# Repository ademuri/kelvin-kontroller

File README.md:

# Kelvin Kontroller

DIY coffee roaster. Custom PCB which controls and monitors the roaster. Has a WiFi dashboard.

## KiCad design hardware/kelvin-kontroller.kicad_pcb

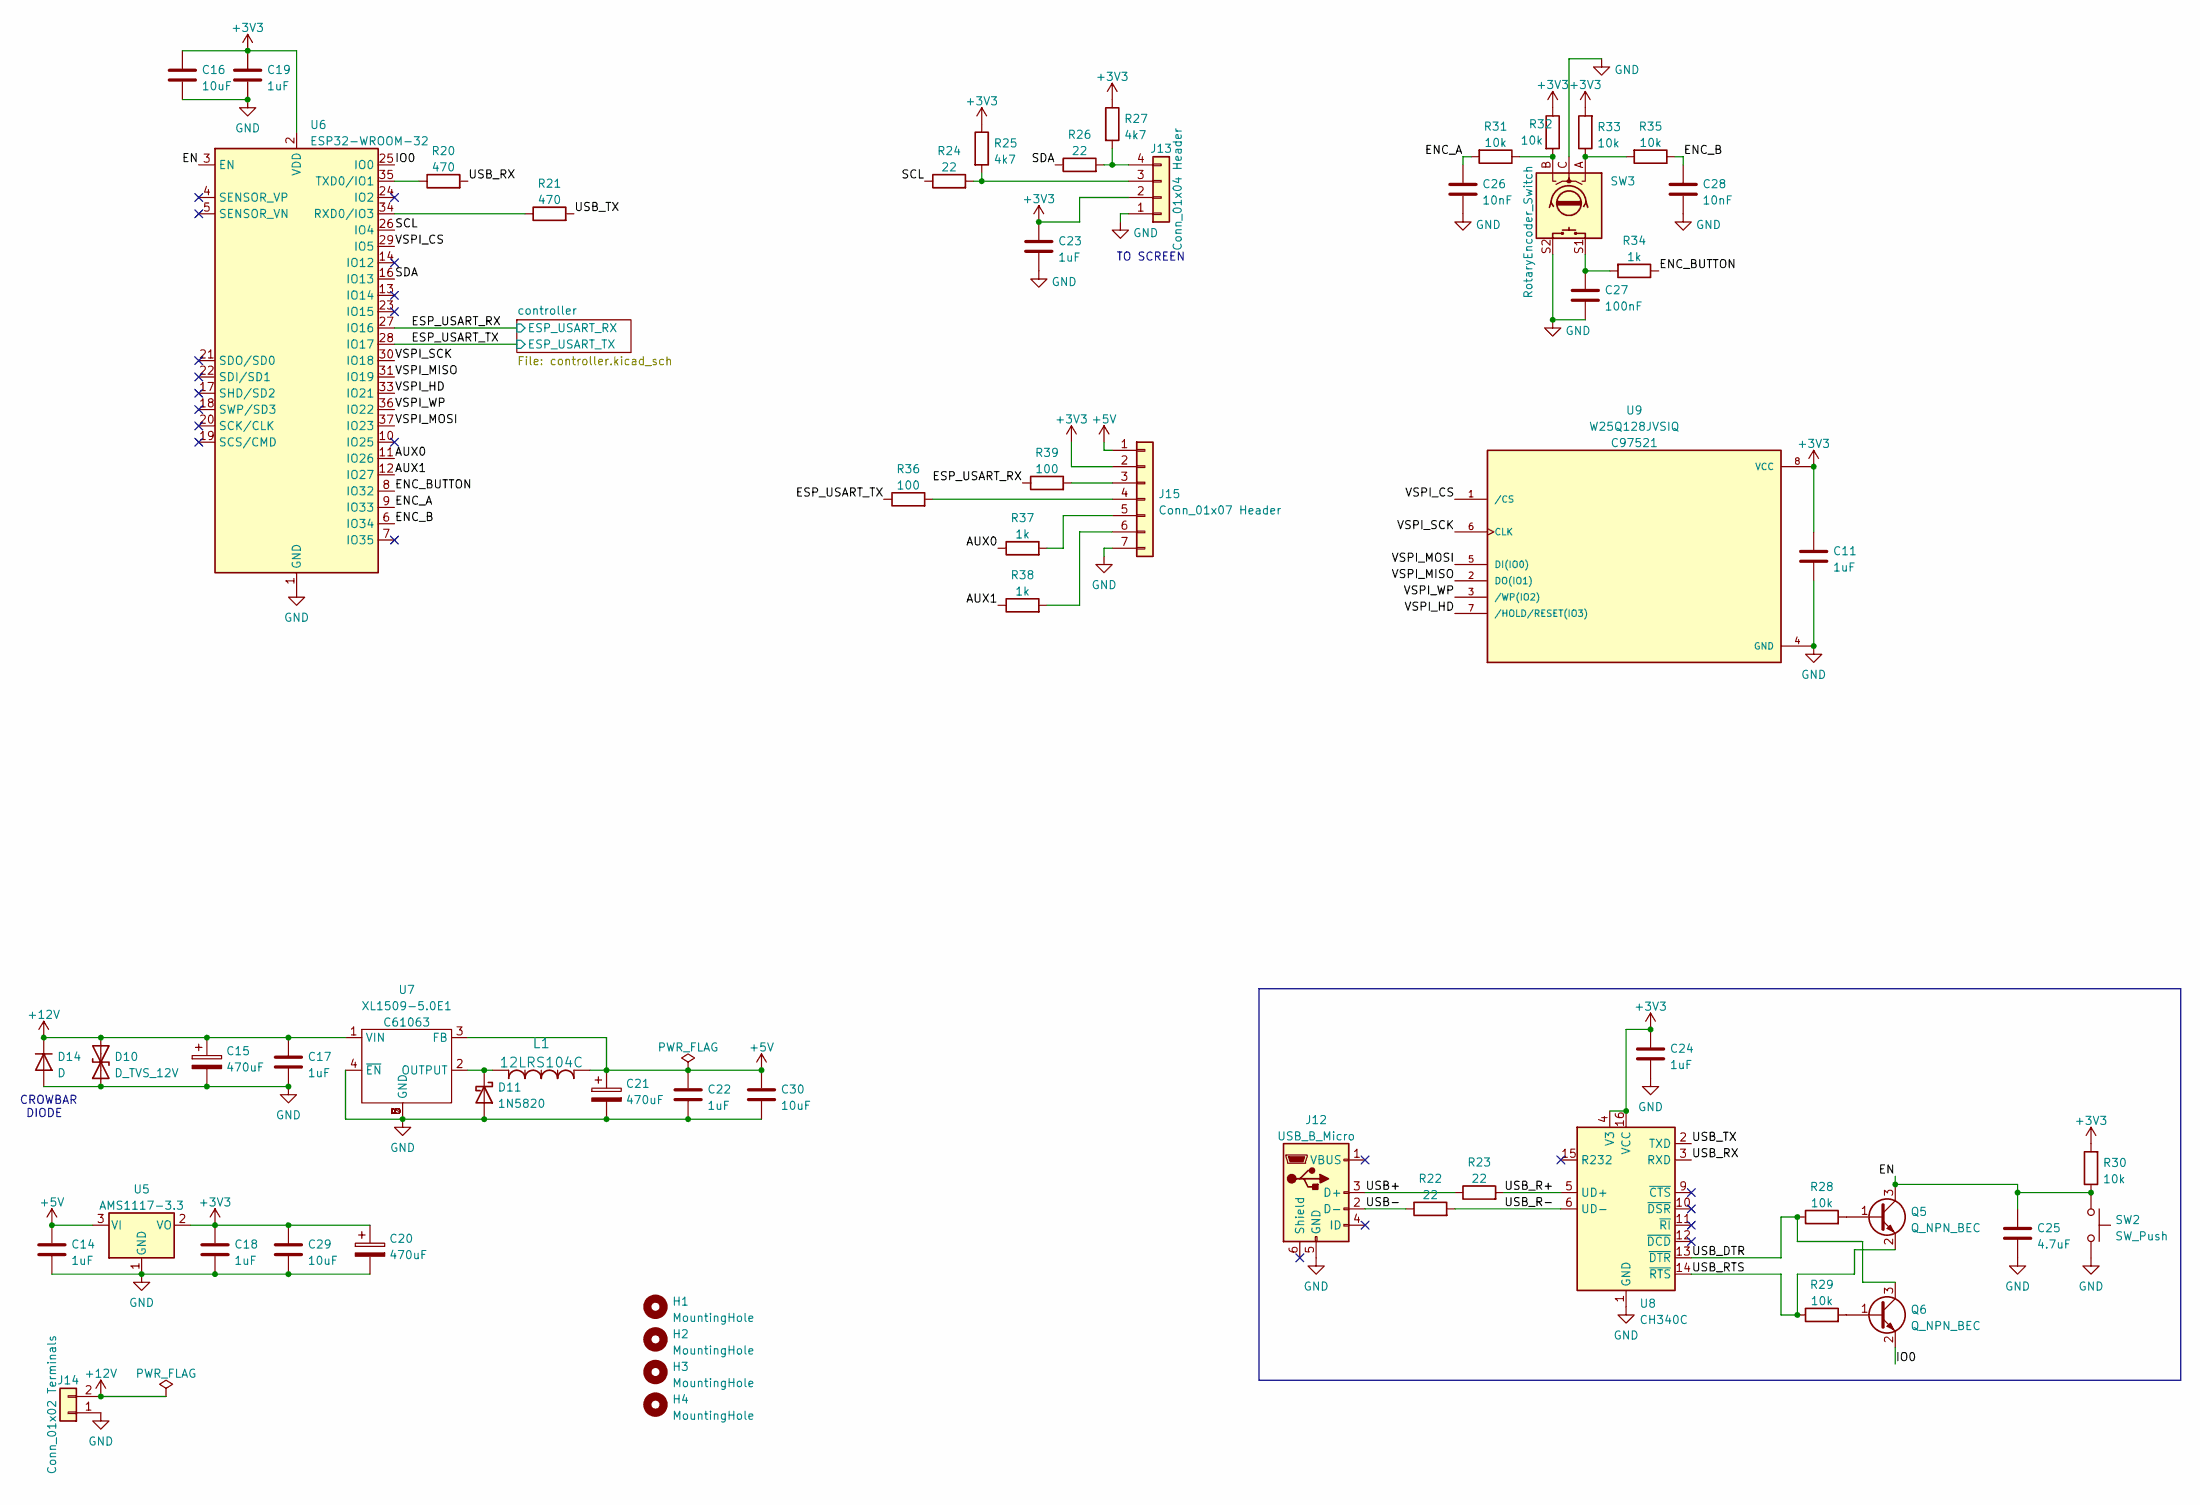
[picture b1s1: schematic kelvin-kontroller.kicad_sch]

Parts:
C11, C14, C17, C18, C19, C22, C23, C24: 1uF; C_0402_1005Metric; LCSC C52923
C15, C20, C21: 470uF; CP_Radial_D10.0mm_P5.00mm; MPN 25PK1000MEFC10X16
C16, C29, C30: 10uF; C_0603_1608Metric; LCSC C96446
C25: 4.7uF; C_0402_1005Metric; LCSC C23733
C26, C28: 10nF; C_0402_1005Metric; LCSC C15195
C27: 100nF; C_0402_1005Metric; LCSC C307331
D10: D_TVS_12V; D_SMA_Handsoldering; MPN 824501131
D11: 1N5820; D_SMA; LCSC C8678
D14: D; D_SMA; LCSC C8678
H1, H2, H3, H4: MountingHole; MountingHole_3.2mm_M3
J12: USB_B_Micro; FRAMATOME_10118194-0001LF_fixed_bridges; LCSC C132563
J13: Conn_01x04 Header; PinHeader_1x04_P2.54mm_Vertical
J14: Conn_01x02 Terminals; Amphenol_BarrierStrip_YK321020XX00G_1x02_P7.62; MPN YK3210203000G
J15: Conn_01x07 Header; PinHeader_1x07_P2.54mm_Vertical
L1: 12LRS104C; MPN 12LRS104C
Q5, Q6: Q_NPN_BEC; SOT-23; LCSC C2150
R20, R21: 470; R_0402_1005Metric; LCSC C25117
R22, R23, R24, R26: 22; R_0402_1005Metric; LCSC C25092
R25, R27: 4k7; R_0402_1005Metric; LCSC C25900
R28, R29, R30, R31, R32, R33, R35: 10k; R_0402_1005Metric; LCSC C25744
R34, R37, R38: 1k; R_0402_1005Metric; LCSC C11702
R36, R39: 100; R_0402_1005Metric; LCSC C25076
SW2: SW_Push; SW_TACTILE_5.1MM_TS-1187A-C-D-B; LCSC C318884
SW3: RotaryEncoder_Switch; BOURNS_PEC12R-4xxxF-Sxxxx; MPN PEC12R-4230F-S0024
U5: AMS1117-3.3; SOT-223-3_TabPin2; LCSC C6186
U6: ESP32-WROOM-32
U7: XL1509-5.0E1; SOIC-8_5.23x5.23mm_P1.27mm; LCSC C61063
U8: CH340C; SOIC-16_3.9x9.9mm_P1.27mm; LCSC C84681
U9: W25Q128JVSIQ; SOIC-8_5.275x5.275mm_P1.27mm; PARTREV I; LCSC C97521

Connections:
+3V3: C11.1, C16.1, C18.1, C19.1, C20.1, C23.1, C24.1, C29.1, J13.2, J15.2, R25.1, R27.1, R30.2, R32.1, R33.2, U5.2 (VO), U6.2 (VDD), U8.4 (V3), U8.16 (VCC), U9.8 (VCC); also elsewhere on the board
+5V: C14.1, C21.1, C22.1, C30.1, J15.1, L1.3, U5.3 (VI), U7.3 (FB); also elsewhere on the board
+12V: C15.1, C17.1, D10.2 (A2), D14.1 (K), J14.2, U7.1 (VIN); also elsewhere on the board
/AUX0: R37.1, U6.11 (IO26)
/AUX1: R38.1, U6.12 (IO27)
/EN: C25.1, Q5.3 (C), R30.1, SW2.1, U6.3 (EN)
/ENC_A: C26.1, R31.2, U6.9 (IO33)
/ENC_B: C28.1, R35.1, U6.6 (IO34)
/ENC_BUTTON: R34.1, U6.8 (IO32)
/ESP_USART_RX: R39.1, U6.27 (IO16); also elsewhere on the board
/ESP_USART_TX: R36.1, U6.28 (IO17); also elsewhere on the board
/IO0: Q6.2 (E), U6.25 (IO0)
/SCL: R24.1, U6.26 (IO4)
/SDA: R26.1, U6.16 (IO13)
/USB+: J12.3 (D+), R23.1
/USB-: J12.2 (D-), R22.1
/USB_DTR: Q6.3 (C), R28.1, U8.13 (~DTR)
/USB_R+: R23.2, U8.5 (UD+)
/USB_R-: R22.2, U8.6 (UD-)
/USB_RTS: Q5.2 (E), R29.1, U8.14 (~RTS)
/USB_RX: R20.2, U8.3 (RXD)
/USB_TX: R21.2, U8.2 (TXD)
/VSPI_CS: U6.29 (IO5), U9.1 (/CS)
/VSPI_HD: U6.33 (IO21), U9.7 (/HOLD/RESET(IO3))
/VSPI_MISO: U6.31 (IO19), U9.2 (DO(IO1))
/VSPI_MOSI: U6.37 (IO23), U9.5 (DI(IO0))
/VSPI_SCK: U6.30 (IO18), U9.6 (CLK)
/VSPI_WP: U6.36 (IO22), U9.3 (/WP(IO2))
GND: C11.2, C14.2, C15.2, C16.2, C17.2, C18.2, C19.2, C20.2, C21.2, C22.2, C23.2, C24.2, C25.2, C26.2, C27.2, C28.2, C29.2, C30.2, D10.1 (A1), D11.2 (A), D14.2 (A), J12.5 (GND), J13.1, J14.1, J15.7, SW2.2, SW3.C, SW3.S2, U5.1 (GND), U6.1 (GND), U6.15 (GND), U6.38 (GND), U6.39 (GND), U7.4 (~EN), U7.5 (GND), U7.6 (GND), U7.7 (GND), U7.8 (GND), U8.1 (GND), U9.4 (GND); also elsewhere on the board
unnamed: C27.1, R34.2, SW3.S1
unnamed: D11.1 (K), L1.1, U7.2 (OUTPUT)
unnamed: J13.3, R24.2, R25.2
unnamed: J13.4, R26.2, R27.2
unnamed: J15.3, R39.2
unnamed: J15.4, R36.2
unnamed: J15.5, R37.2
unnamed: J15.6, R38.2
unnamed: Q5.1 (B), R28.2
unnamed: Q6.1 (B), R29.2
unnamed: R20.1, U6.35 (TXD0/IO1)
unnamed: R21.1, U6.34 (RXD0/IO3)
unnamed: R31.1, R32.2, SW3.B
unnamed: R33.1, R35.2, SW3.A

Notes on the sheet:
CROWBAR DIODE
TO SCREEN

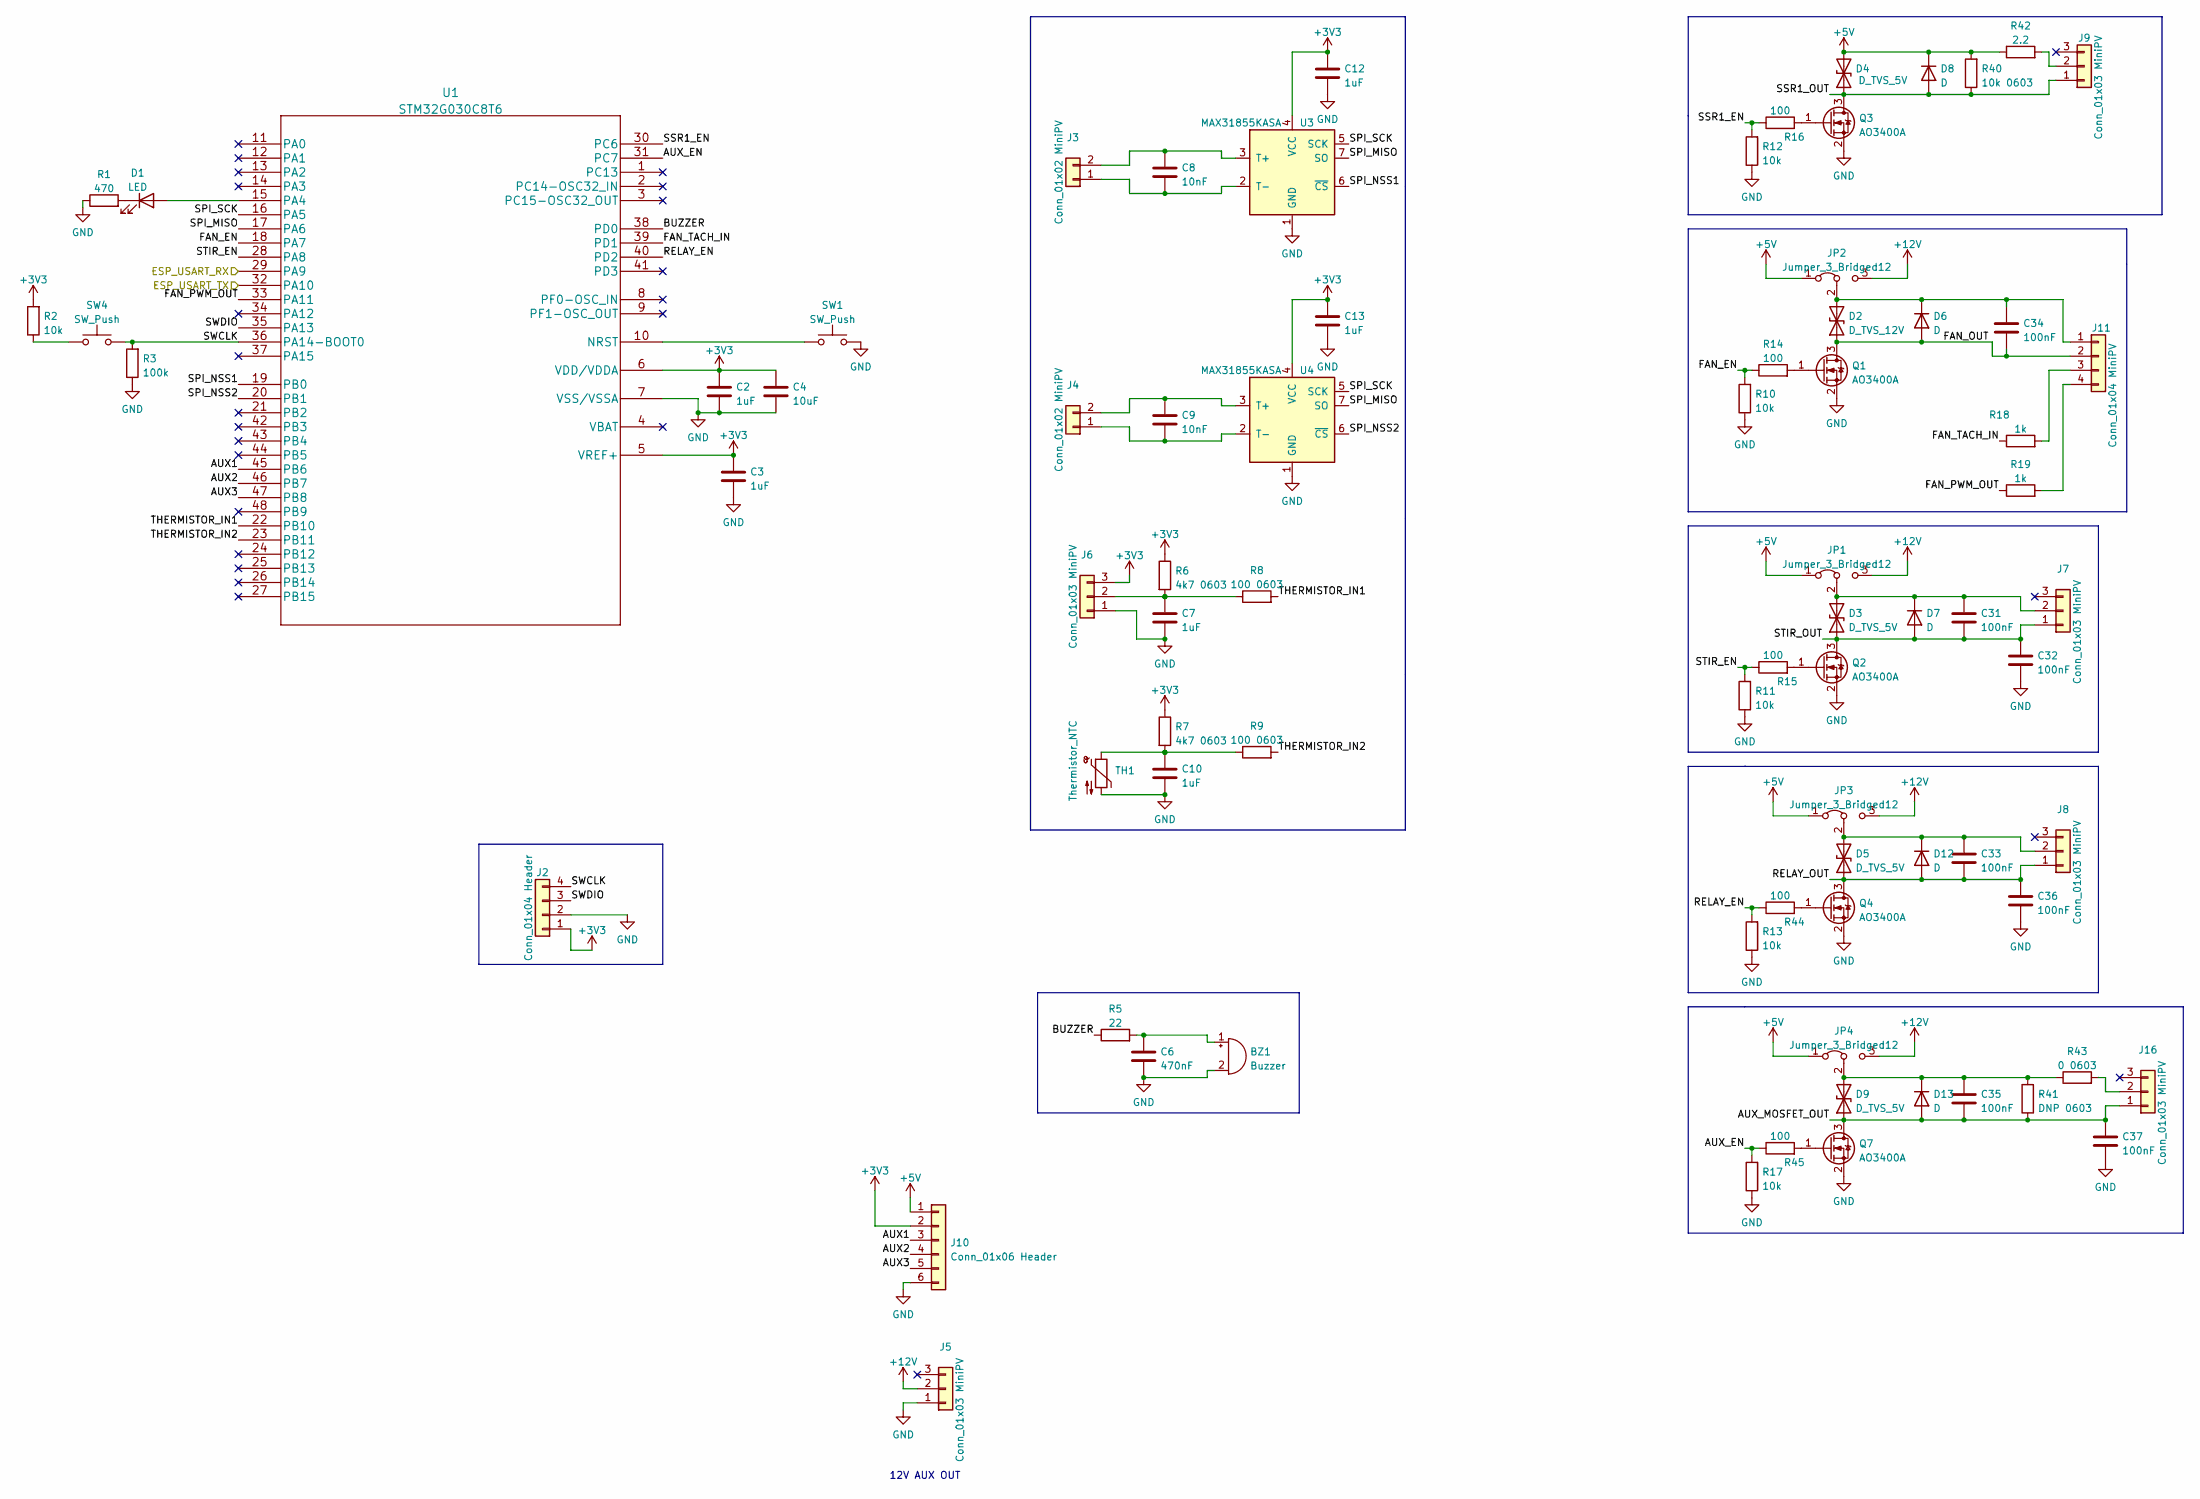
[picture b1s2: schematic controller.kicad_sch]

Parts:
BZ1: Buzzer; MURATA_PKM13EPYH4000-A0; MPN PKM13EPYH4000-A0
C2, C3, C7, C10, C12, C13: 1uF; C_0402_1005Metric; LCSC C52923
C4: 10uF; C_0603_1608Metric; LCSC C96446
C6: 470nF; C_0402_1005Metric; LCSC C47339
C8, C9: 10nF; C_0402_1005Metric; LCSC C15195
C31, C32, C33, C34, C35, C36, C37: 100nF; C_0402_1005Metric; LCSC C307331
D1: LED; LED_0805_2012Metric; LCSC C84256
D2: D_TVS_12V; D_SMA_Handsoldering; MPN 824501131
D3, D4, D5, D9: D_TVS_5V; D_SMA_Handsoldering; MPN 824501600
D6, D7, D8, D12, D13: D; D_SMA; LCSC C8678
J2: Conn_01x04 Header; PinHeader_1x04_P2.54mm_Vertical
J3, J4: Conn_01x02 MiniPV; MiniPV_76384-X02XX_1x02_P2.54mm_Vertical
J5, J6, J7, J8, J9, J16: Conn_01x03 MiniPV; MiniPV_69167-X03XXX_1x03_P2.54mm_Polarized_Vertical
J10: Conn_01x06 Header; PinHeader_1x06_P2.54mm_Vertical
J11: Conn_01x04 MiniPV; MiniPV_69167-X04XXX_1x04_P2.54mm_Polarized_Vertical
JP1, JP2, JP3, JP4: Jumper_3_Bridged12; PinHeader_1x03_P2.54mm_Vertical
Q1, Q2, Q3, Q4, Q7: AO3400A; SOT-23; LCSC C20917
R1: 470; R_0402_1005Metric; LCSC C25117
R2, R10, R11, R12, R13, R17: 10k; R_0402_1005Metric; LCSC C25744
R3: 100k; R_0402_1005Metric; LCSC C25741
R5: 22; R_0402_1005Metric; LCSC C25092
R6, R7: 4k7 0603; R_0603_1608Metric_Pad0.98x0.95mm_HandSolder; LCSC C23162
R8, R9: 100 0603; R_0603_1608Metric_Pad0.98x0.95mm_HandSolder; LCSC C22775
R14, R15, R16, R44, R45: 100; R_0402_1005Metric; LCSC C25076
R18, R19: 1k; R_0402_1005Metric; LCSC C11702
R40: 10k 0603; R_0603_1608Metric_Pad0.98x0.95mm_HandSolder; LCSC C25804
R41: DNP 0603; R_0603_1608Metric_Pad0.98x0.95mm_HandSolder; LCSC C25804
R42: 2.2; R_0603_1608Metric_Pad0.98x0.95mm_HandSolder; LCSC C22939
R43: 0 0603; R_0603_1608Metric_Pad0.98x0.95mm_HandSolder; LCSC C22939
SW1, SW4: SW_Push; SW_TACTILE_5.1MM_TS-1187A-C-D-B; LCSC C318884
TH1: Thermistor_NTC; C_Disc_D3.0mm_W2.0mm_P2.50mm; MPN NXRT15XH103FA1B030
U1: STM32G030C8T6; LQFP-48_7x7mm_P0.5mm; LCSC C529329
U3, U4: MAX31855KASA; SOIC-8_3.9x4.9mm_P1.27mm; LCSC C52028

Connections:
+3V3: C2.1, C3.1, C4.1, C12.1, C13.1, J2.1, J6.3, J10.2, R2.2, R6.1, R7.1, U1.5 (VREF+), U1.6 (VDD/VDDA), U3.4 (VCC), U4.4 (VCC); also elsewhere on the board
+5V: D4.2 (A2), D8.1 (K), J10.1, JP1.1 (A), JP2.1 (A), JP3.1 (A), JP4.1 (A), R40.2, R42.1; also elsewhere on the board
+12V: J5.2, JP1.3 (B), JP2.3 (B), JP3.3 (B), JP4.3 (B); also elsewhere on the board
/ESP_USART_RX: U1.29 (PA9); also elsewhere on the board
/ESP_USART_TX: U1.32 (PA10); also elsewhere on the board
/controller/AUX1: J10.3, U1.45 (PB6)
/controller/AUX2: J10.4, U1.46 (PB7)
/controller/AUX3: J10.5, U1.47 (PB8)
/controller/AUX_EN: R17.2, R45.1, U1.31 (PC7)
/controller/AUX_MOSFET_OUT: C35.2, C37.1, D9.1 (A1), D13.2 (A), J16.1, Q7.3 (D), R41.1
/controller/BUZZER: R5.1, U1.38 (PD0)
/controller/FAN_EN: R10.2, R14.1, U1.18 (PA7)
/controller/FAN_OUT: C34.2, D2.1 (A1), D6.2 (A), J11.2, Q1.3 (D)
/controller/FAN_PWM_OUT: R19.1, U1.33 (PA11)
/controller/FAN_TACH_IN: R18.1, U1.39 (PD1)
/controller/RELAY_EN: R13.2, R44.1, U1.40 (PD2)
/controller/RELAY_OUT: C33.2, C36.1, D5.1 (A1), D12.2 (A), J8.1, Q4.3 (D)
/controller/SPI_MISO: U1.17 (PA6), U3.7 (SO), U4.7 (SO)
/controller/SPI_NSS1: U1.19 (PB0), U3.6 (~CS)
/controller/SPI_NSS2: U1.20 (PB1), U4.6 (~CS)
/controller/SPI_SCK: U1.16 (PA5), U3.5 (SCK), U4.5 (SCK)
/controller/SSR1_EN: R12.2, R16.1, U1.30 (PC6)
/controller/SSR1_OUT: D4.1 (A1), D8.2 (A), J9.1, Q3.3 (D), R40.1
/controller/STIR_EN: R11.2, R15.1, U1.28 (PA8)
/controller/STIR_OUT: C31.2, C32.1, D3.1 (A1), D7.2 (A), J7.1, Q2.3 (D)
/controller/SWCLK: J2.4, R3.2, SW4.2, U1.36 (PA14-BOOT0)
/controller/SWDIO: J2.3, U1.35 (PA13)
/controller/THERMISTOR_IN1: R8.2, U1.22 (PB10)
/controller/THERMISTOR_IN2: R9.2, U1.23 (PB11)
GND: BZ1.2 (+), C2.2, C3.2, C4.2, C6.2, C7.2, C10.2, C12.2, C13.2, C32.2, C36.2, C37.2, J2.2, J5.1, J6.1, J10.6, Q1.2 (S), Q2.2 (S), Q3.2 (S), Q4.2 (S), Q7.2 (S), R1.1, R3.1, R10.1, R11.1, R12.1, R13.1, R17.1, SW1.2, TH1.2, U1.7 (VSS/VSSA), U3.1 (GND), U4.1 (GND); also elsewhere on the board
unnamed: BZ1.1 (-), C6.1, R5.2
unnamed: C7.1, J6.2, R6.2, R8.1
unnamed: C8.1, J3.2, U3.3 (T+)
unnamed: C8.2, J3.1, U3.2 (T-)
unnamed: C9.1, J4.2, U4.3 (T+)
unnamed: C9.2, J4.1, U4.2 (T-)
unnamed: C10.1, R7.2, R9.1, TH1.1
unnamed: C31.1, D3.2 (A2), D7.1 (K), J7.2, JP1.2 (C)
unnamed: C33.1, D5.2 (A2), D12.1 (K), J8.2, JP3.2 (C)
unnamed: C34.1, D2.2 (A2), D6.1 (K), J11.1, JP2.2 (C)
unnamed: C35.1, D9.2 (A2), D13.1 (K), JP4.2 (C), R41.2, R43.1
unnamed: D1.1 (K), R1.2
unnamed: D1.2 (A), U1.15 (PA4)
unnamed: J9.2, R42.2
unnamed: J11.3, R18.2
unnamed: J11.4, R19.2
unnamed: J16.2, R43.2
unnamed: Q1.1 (G), R14.2
unnamed: Q2.1 (G), R15.2
unnamed: Q3.1 (G), R16.2
unnamed: Q4.1 (G), R44.2
unnamed: Q7.1 (G), R45.2
unnamed: R2.1, SW4.1
unnamed: SW1.1, U1.10 (NRST)

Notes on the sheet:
12V AUX OUT

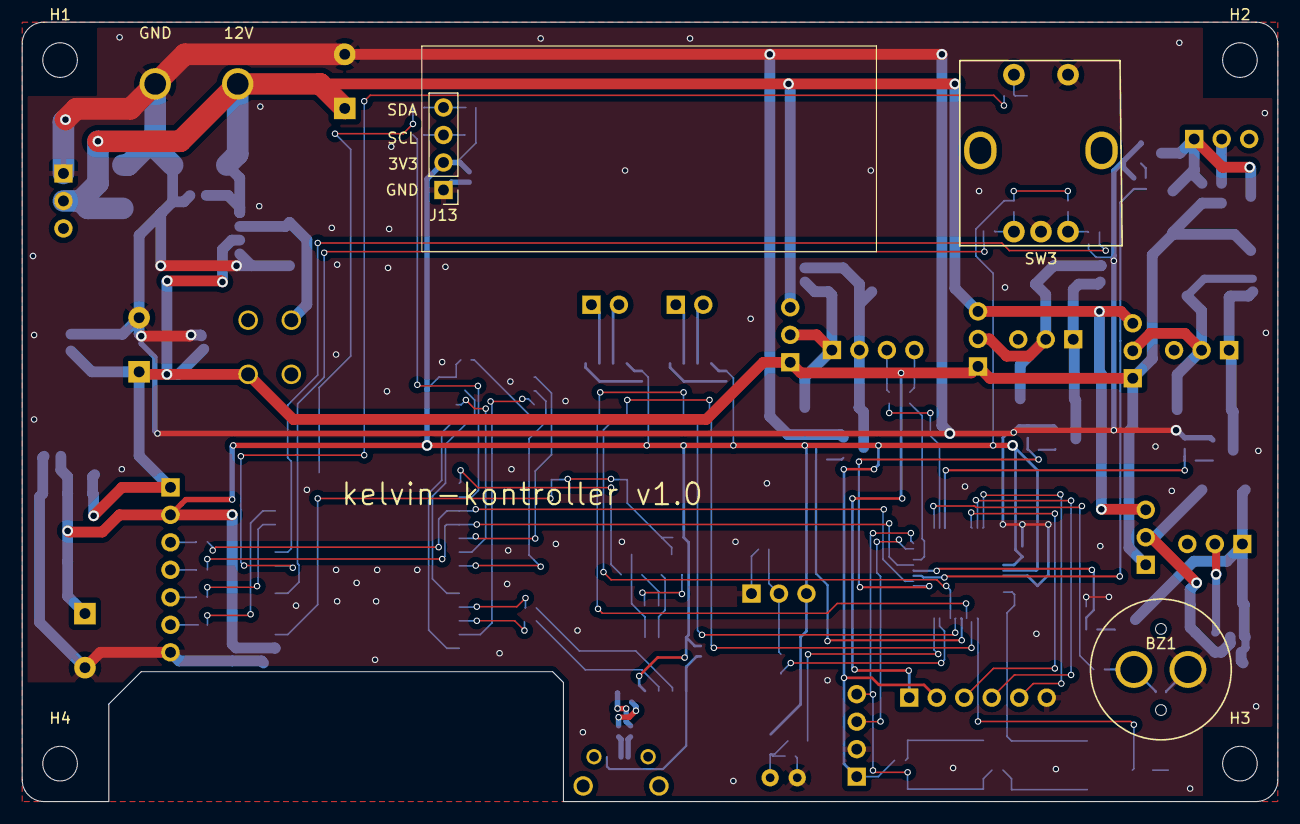
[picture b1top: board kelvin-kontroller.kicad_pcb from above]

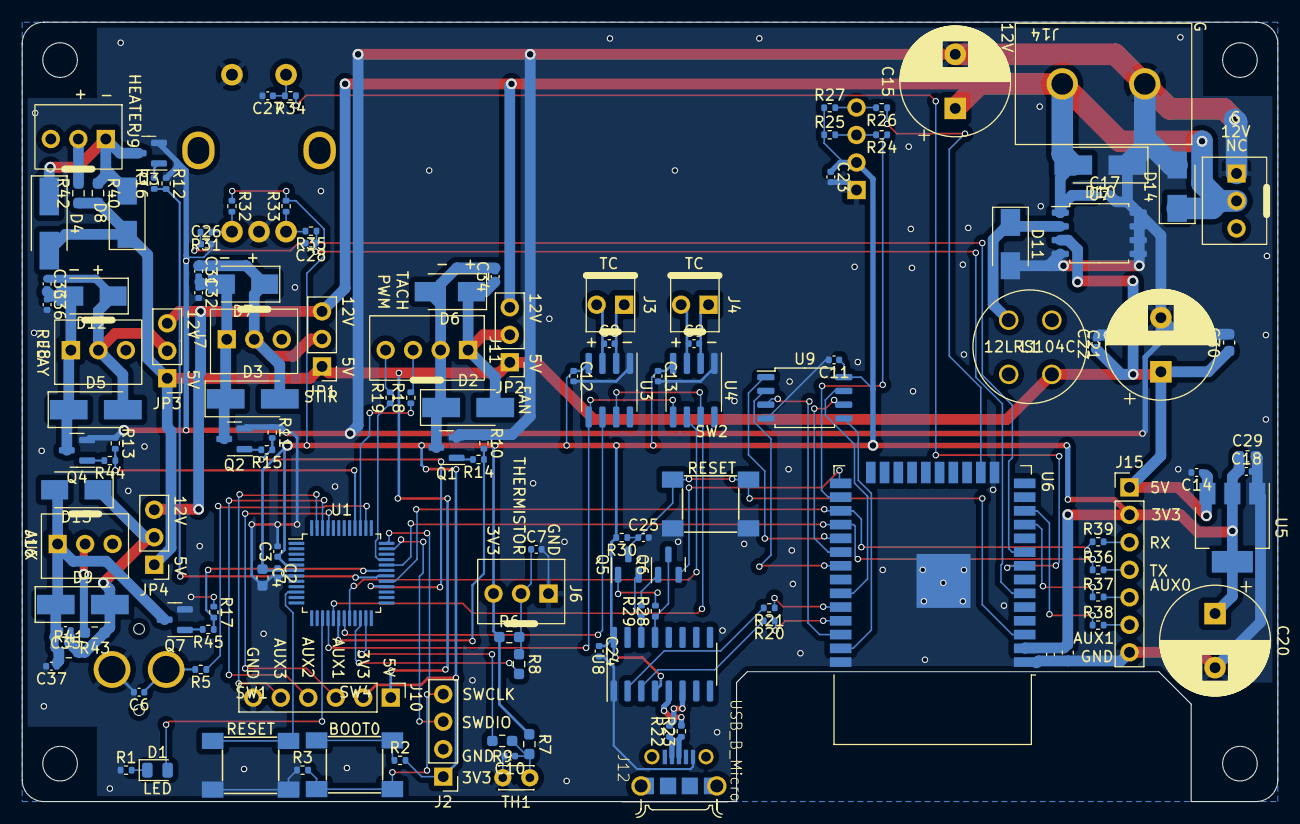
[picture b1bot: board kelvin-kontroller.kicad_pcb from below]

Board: 2 copper layers, 116.0 x 72.0 mm, 138 parts (131 on the bottom side), 91 nets.

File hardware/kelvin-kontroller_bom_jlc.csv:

"Comment","Designator","Footprint","LCSC Part #"
"470nF","C6","C_0402_1005Metric","C47339"
"1uF","C11,C14,C17,C18,C19,C22,C23,C24,C2,C3,C7,C10,C12,C13","C_0402_1005Metric","C52923"
"10uF","C16,C29,C30,C4","C_0603_1608Metric","C96446"
"4.7uF","C25","C_0402_1005Metric","C23733"
"10nF","C26,C28,C8,C9","C_0402_1005Metric","C15195"
"100nF","C27,C31,C32,C33,C34,C35,C36,C37","C_0402_1005Metric","C307331"
"LED","D1","LED_0805_2012Metric","C84256"
"1N5820","D11","D_SMA","C8678"
"D","D14,D6,D7,D8,D12,D13","D_SMA","C8678"
"USB_B_Micro","J12","FRAMATOME_10118194-0001LF_fixed_bridges","C132563"
"AO3400A","Q1,Q2,Q3,Q4,Q7","SOT-23","C20917"
"Q_NPN_BEC","Q5,Q6","SOT-23","C2150"
"100k","R3","R_0402_1005Metric","C25741"
"4k7 0603","R6,R7","R_0603_1608Metric_Pad0.98x0.95mm_HandSolder","C23162"
"100 0603","R8,R9","R_0603_1608Metric_Pad0.98x0.95mm_HandSolder","C22775"
"470","R20,R21,R1","R_0402_1005Metric","C25117"
"22","R22,R23,R24,R26,R5","R_0402_1005Metric","C25091"
"4k7","R25,R27","R_0402_1005Metric","C25900"
"10k","R28,R29,R30,R31,R32,R33,R35,R2,R10,R11,R12,R13,R17","R_0402_1005Metric","C25744"
"1k","R34,R37,R38,R18,R19","R_0402_1005Metric","C11702"
"100","R36,R39,R14,R15,R16,R44,R45","R_0402_1005Metric","C25076"
"10k 0603","R40","R_0603_1608Metric_Pad0.98x0.95mm_HandSolder","C25804"
"DNP 0603","R41","R_0603_1608Metric_Pad0.98x0.95mm_HandSolder","C25804"
"2.2","R42","R_0603_1608Metric_Pad0.98x0.95mm_HandSolder","C22939"
"0 0603","R43","R_0603_1608Metric_Pad0.98x0.95mm_HandSolder","C22939"
"SW_Push","SW2,SW1,SW4","SW_TACTILE_5.1MM_TS-1187A-C-D-B","C318884"
"STM32G030C8T6","U1","LQFP-48_7x7mm_P0.5mm","C529329"
"MAX31855KASA","U3,U4","SOIC-8_3.9x4.9mm_P1.27mm","C52028"
"AMS1117-3.3","U5","SOT-223-3_TabPin2","C6186"
"XL1509-5.0E1","U7","SOIC-8_5.23x5.23mm_P1.27mm","C61063"
"CH340C","U8","SOIC-16_3.9x9.9mm_P1.27mm","C84681"
"W25Q128JVSIQ","U9","SOIC-8_5.275x5.275mm_P1.27mm","C97521"

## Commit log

2022-10-03 Start adding schematic
2022-10-04 Add KiCAD gitignore
2022-10-04 Continue schematic - finish controller and add LCD
2022-10-05 Schematic nearly finished
2022-10-06 Update schematic and part assignment
2022-10-06 Add readme and license
2022-10-07 Finish assigning footprints
2022-10-10 Start layout
2022-10-11 Add internal thermistor and change SSR2 -> mosfet
2022-10-11 Continue layout, add SPI flash
2022-10-12 Continue layout
2022-10-13 First pass at layout
2022-10-13 Start routing
2022-10-14 Hardware revision v1.0
2022-10-16 Init platformio for both mcus
2022-10-16 Add pin definitions for stm32
2022-10-18 Add controls for heater, and min/max settings
2022-10-18 Add github actions config
2022-10-18 Add getters and stir control to controller
2022-10-18 Add Init and Step to controller
2022-10-18 Start adding thermistor class (not working yet)
2022-10-19 Fix thermistor and add Celsius/Fahrenheit methods
2022-10-19 Enable ASAN and UBSAN for tests
2022-10-19 Configure CI to run tests
2022-10-19 Format thermistor files
2022-10-20 Add function to read resistance to thermistor
2022-10-20 Add ReadFahrenheit convenience method
2022-10-20 Add thermocouple classes
2022-10-21 Initialize SPI
2022-10-21 Add filtering for temps
2022-10-22 Add basic error handling to runner
2022-10-22 Start adding test coverage for controller
2022-10-22 Complete test coverage for controller min/max temps
2022-10-22 Check that the controller turns on the relay at init
2022-10-22 Check for thermocouple read errors in controller
2022-10-22 Set temps in RunnerStatus
2022-10-22 Change heater to be on/off in the controller
2022-10-22 Add a command struct
2022-10-22 Add lint script and format files
2022-10-25 Add serial comms to runner
2022-10-25 Start adding websockets support
    Currently untested.
2022-10-26 Use easy transfer between esp32 and stm32
2022-10-26 Add a comms timeout to controller
2022-10-27 Fault on no comms
2022-10-27 Switch from websockets to modbus and implement read
2022-10-28 Mostly add modbus write
2022-10-28 Revert "Mostly add modbus write"
    This reverts commit 60ff8b54a95f325f4c3ebfb928f32a231f997c20.
2022-10-28 Revert "Switch from websockets to modbus and implement read"
    This reverts commit 17dc94d3522de2c36d9289a8d3dcdf5e81051fe6.
2022-10-28 Add support for setting temp, fan, and reset over websockets
2022-10-30 Fix string constants definitions
2022-10-30 Add basic screen output
2022-10-31 Updates from pcb testing:
    - Switch to defining serial port via flags
    - Don't use the thermocouples yet, as they do not work
    - Set nBOOT_SEL = 0, to make the BOOT0 button work
2022-10-31 Start adding STM32 flashing to ESP32
2022-10-31 Switch to fastified version of MAX31855 library
2022-10-31 Increase dashboard refresh to 1s
2022-11-01 Fix thermocouple scaling
2022-11-01 Add HTML dashboard
2022-11-01 Fix ambient temp
2022-11-01 Add display to oled
2022-11-01 Fix startup faults and commands
2022-11-01 Oled cleanup
2022-11-05 Migrate to refactored version of EasyTransfer
2022-11-05 Allow setting PID params from dashboard
2022-11-05 Decrease therm filter interval
2022-11-05 Add plot to dashboard
2022-11-05 Allowed greater patch versions of esp32 lib deps
2022-11-05 Decrease therm filter run interval slightly
2022-11-05 Embiggen plot
2022-11-05 Display heater output on graph
2022-11-05 Only enable heater if fan is on
2022-11-05 Prepare for PID tuning
2022-11-06 Stir when the temperature is above a threshold
2022-11-06 Fix tests
2022-11-06 Set fan *target* from the command
2022-11-06 Run the fan while hot.
    Also add test coverage for stirring while hot.
2022-11-06 Add turn-on delay for control loop
2022-11-06 Report thermocouple error codes
2022-11-06 Seperate faults into since-reset and fatal
2022-11-06 Add test coverage for fatal fault
2022-11-07 Add CSV output to dashboard
2023-01-15 Increase temp limits
2023-03-11 Pin dep versions
2023-03-11 Update test temps to fix breakage from updated temp thresholds
2023-03-11 Update KiCAD files to v7
2023-03-11 Update CI action deps
2023-03-11 Migrate fan to be direct PWM
2023-03-11 Update dep package specs to allow compatible changes
2023-03-13 Improve dashboard
    - Don't stomp on user changes to the graph scale
    - Make graph and controls side-by-side
    - Add button to reset the graph
    - Add header to CSV output
2023-03-13 Display fatal fault status on dashboard
2023-03-13 Tune fan for direct fan control
2023-03-13 Fix dashboard graph autoscale logic
2023-03-13 Increase noise filtering on thermocouples
2023-03-14 Save PID values to browser local storage
2023-03-14 Add roast progress buttons
2023-03-14 Fix graph annotations
2023-03-20 Add OTA support for ESP32
2023-03-20 Add dashboard support for running a curve
2023-03-20 Set the hostname for ArduinoOTA
2023-03-20 Implement curves on the esp32
2023-03-20 Fix curve implementation and silence debug serial messages by default
2023-03-20 Add curve stop and fix set temp display
2023-03-20 Add curve pause
2023-03-20 Add a button to go to the next curve point
2023-03-20 Reset the stm32 on esp32 boot
2023-03-20 Fix temp to be a float in the curve
2023-03-23 Switch to pid on env temp
2023-03-23 Fix build breakage
2023-03-23 Only update set temp when it's not being edited
2023-03-23 Ignore relay status in shutdown logic
2023-03-23 Reset annotations when resetting graph
2023-03-23 Dashboard: cap temps and fix fan and set temp background updating
2023-03-23 Temporarily disable bean temp error checking
2023-03-23 Revert "Temporarily disable bean temp error checking"
    This reverts commit b2ad6d23c0a7b395710909d4146182cc1b9ba5fb.
2023-03-23 Update PID test to use env temp
2023-03-23 Add delay between turning on fan and heater
2023-03-23 Add ramper library
2023-03-23 Ramp up the fan when turning it on
2023-03-25 Revert "Revert "Temporarily disable bean temp error checking""
    This reverts commit 0b898d0423451fecd327621fa275b2952f871731.
2023-03-25 Fix annotations
2023-04-21 Fix tests - account for fan ramping
2023-04-21 Add ramping to set temp
2023-04-21 Add target temp to dashboard
2023-05-06 Add support for manually overriding the heater output
2023-05-06 Shorten error messages
2023-05-07 Fix setpoint display
2023-05-07 Reduce fault sensitivity
2023-05-07 Make dashboard work with manually setting the heater
2023-07-09 Change curve to use manual_output instead of target temp
2023-07-09 Sound buzzer when a fatal fault occurs
2023-07-09 Add cooldown logic
2023-07-10 Update manual output control during curve
2023-08-02 Fix cooldown and stop to stop curve
2023-10-07 Fix fault fan bug and auto-reset after fault
2024-10-14 Add stop-at to dashboard
2024-10-14 Decrease cooldown temp
2024-10-14 Add light dashboard
2024-11-06 Fix out-of-memory compile error
2024-11-07 Update dependencies for esp32
2024-11-07 Update timer library version
2025-01-26 Convert to KiCAD 8 and remove BOM files
2025-01-26 Add .gitignore for KiCAD

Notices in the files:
parts and their libraries:
Copyright 2021 Accelerated Designs. All rights reserved.
